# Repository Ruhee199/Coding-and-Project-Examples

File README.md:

# Coding-and-Project-Examples
Below you will find various files relating to PCB and Photodiode development through KiCAD.

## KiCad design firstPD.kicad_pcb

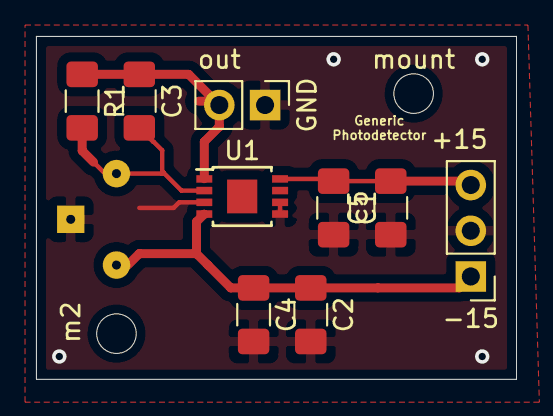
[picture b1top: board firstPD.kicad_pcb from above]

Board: 2 copper layers, 26.7 x 19.0 mm, 12 parts (1 on the bottom side), 5 nets.

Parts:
-15: Power; PinHeader_1x03_P2.54mm_Vertical
C1: 100n; C_1206_3216Metric_Pad1.42x1.75mm_HandSolder
C2: 1u; C_1206_3216Metric_Pad1.42x1.75mm_HandSolder
C3: 18p; C_1206_3216Metric_Pad1.42x1.75mm_HandSolder
C4, C5: 10n; C_1206_3216Metric_Pad1.42x1.75mm_HandSolder
GND: Output; PinHeader_1x02_P2.54mm_Vertical
PD: FDS100
R1: 8k06; R_1206_3216Metric_Pad1.42x1.75mm_HandSolder
U1: ADA4661-2; MSOP-8-1EP_3x3mm_P0.65mm_EP1.68x1.88mm
m2: MountingHole_2.2mm_M2
mount: MountingHole_2.2mm_M2

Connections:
+15V: -15.3, C1.1, C5.2, U1.8
-15V: -15.1, C2.1, C4.1, PD.1, U1.4
GND: -15.2, C1.2, C2.2, C4.2, C5.1, GND.1, PD.2, U1.3, U1.5, U1.6
unnamed: C3.1, GND.2, R1.1, U1.1
unnamed: C3.2, PD.3, R1.2, U1.2

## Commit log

2020-04-01 Create Photodiode Detectors
2020-05-26 Add files via upload
    Jupyter notebook detailing code and data needed to find the mass and mass to luminosity ratio of the Coma Cluster.
2020-10-29 Add files via upload
    Moment 0 and Moment 1 maps for the object BHR_C18O. There are maps for co,13co, and c18o.
2020-10-29 Add files via upload
    Moment 0 and 1 maps for BHR_c18o. There are maps for the molecules co, 13co, and c18o.
